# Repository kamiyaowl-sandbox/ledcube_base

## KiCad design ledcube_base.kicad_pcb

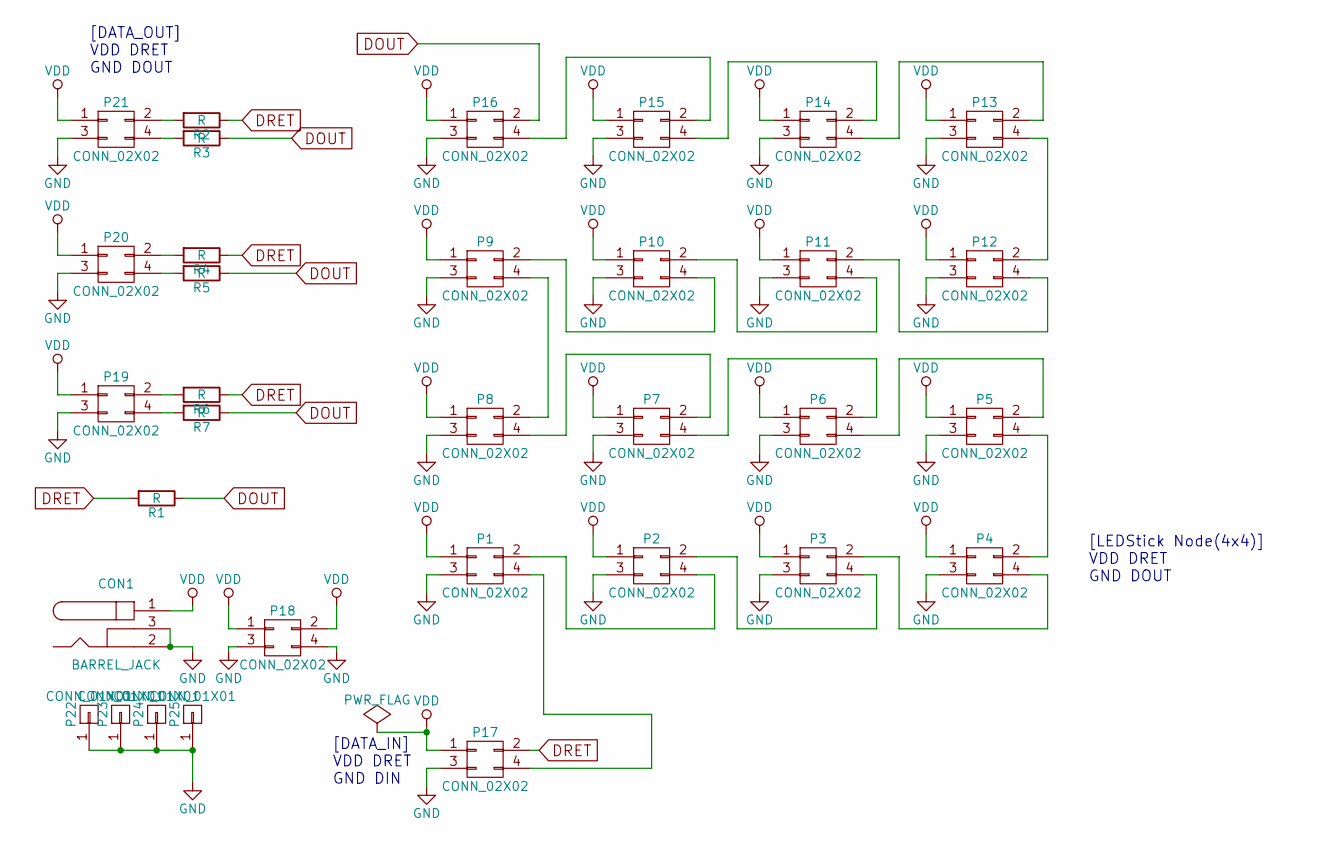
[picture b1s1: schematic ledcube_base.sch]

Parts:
CON1: BARREL_JACK
P1, P2, P3, P4, P5, P6, P7, P8, P9, P10, P11, P12, P13, P14, P15, P16: CONN_02X02; Pin_Header_Straight_2x02
P17: CONN_02X02; Socket_Strip_Angled_2x02
P18: CONN_02X02; Socket_Strip_Straight_2x02
P19, P20, P21: CONN_02X02; Pin_Header_Angled_2x02
P22, P23, P24, P25: CONN_01X01; M3_Drill
R1, R2, R3, R4, R5, R6, R7: R; HANDSOL_0603

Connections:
DOUT: P16.2, R1.1, R3.1, R5.1, R7.1
DRET: P17.2, R1.2, R2.1, R4.1, R6.1
GND: CON1.2, CON1.3, P1.3, P2.3, P3.3, P4.3, P5.3, P6.3, P7.3, P8.3, P9.3, P10.3, P11.3, P12.3, P13.3, P14.3, P15.3, P16.3, P17.3, P18.3, P18.4, P19.3, P20.3, P21.3, P22.1, P23.1, P24.1, P25.1
unnamed: P1.2, P2.4
unnamed: P1.4, P17.4
unnamed: P2.2, P3.4
unnamed: P3.2, P4.4
unnamed: P4.2, P5.4
unnamed: P5.2, P6.4
unnamed: P6.2, P7.4
unnamed: P7.2, P8.4
unnamed: P8.2, P9.4
unnamed: P10.2, P11.4
unnamed: P9.2, P10.4
unnamed: P11.2, P12.4
unnamed: P12.2, P13.4
unnamed: P13.2, P14.4
unnamed: P14.2, P15.4
unnamed: P15.2, P16.4
unnamed: P19.2, R6.2
unnamed: P19.4, R7.2
unnamed: P20.2, R4.2
unnamed: P20.4, R5.2
unnamed: P21.2, R2.2
unnamed: P21.4, R3.2
VDD: CON1.1, P1.1, P2.1, P3.1, P4.1, P5.1, P6.1, P7.1, P8.1, P9.1, P10.1, P11.1, P12.1, P13.1, P14.1, P15.1, P16.1, P17.1, P18.1, P18.2, P19.1, P20.1, P21.1

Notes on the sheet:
[LEDStick Node(4x4)] VDD DRET GND DOUT
[DATA_IN] VDD DRET GND DIN
[DATA_OUT] VDD DRET GND DOUT

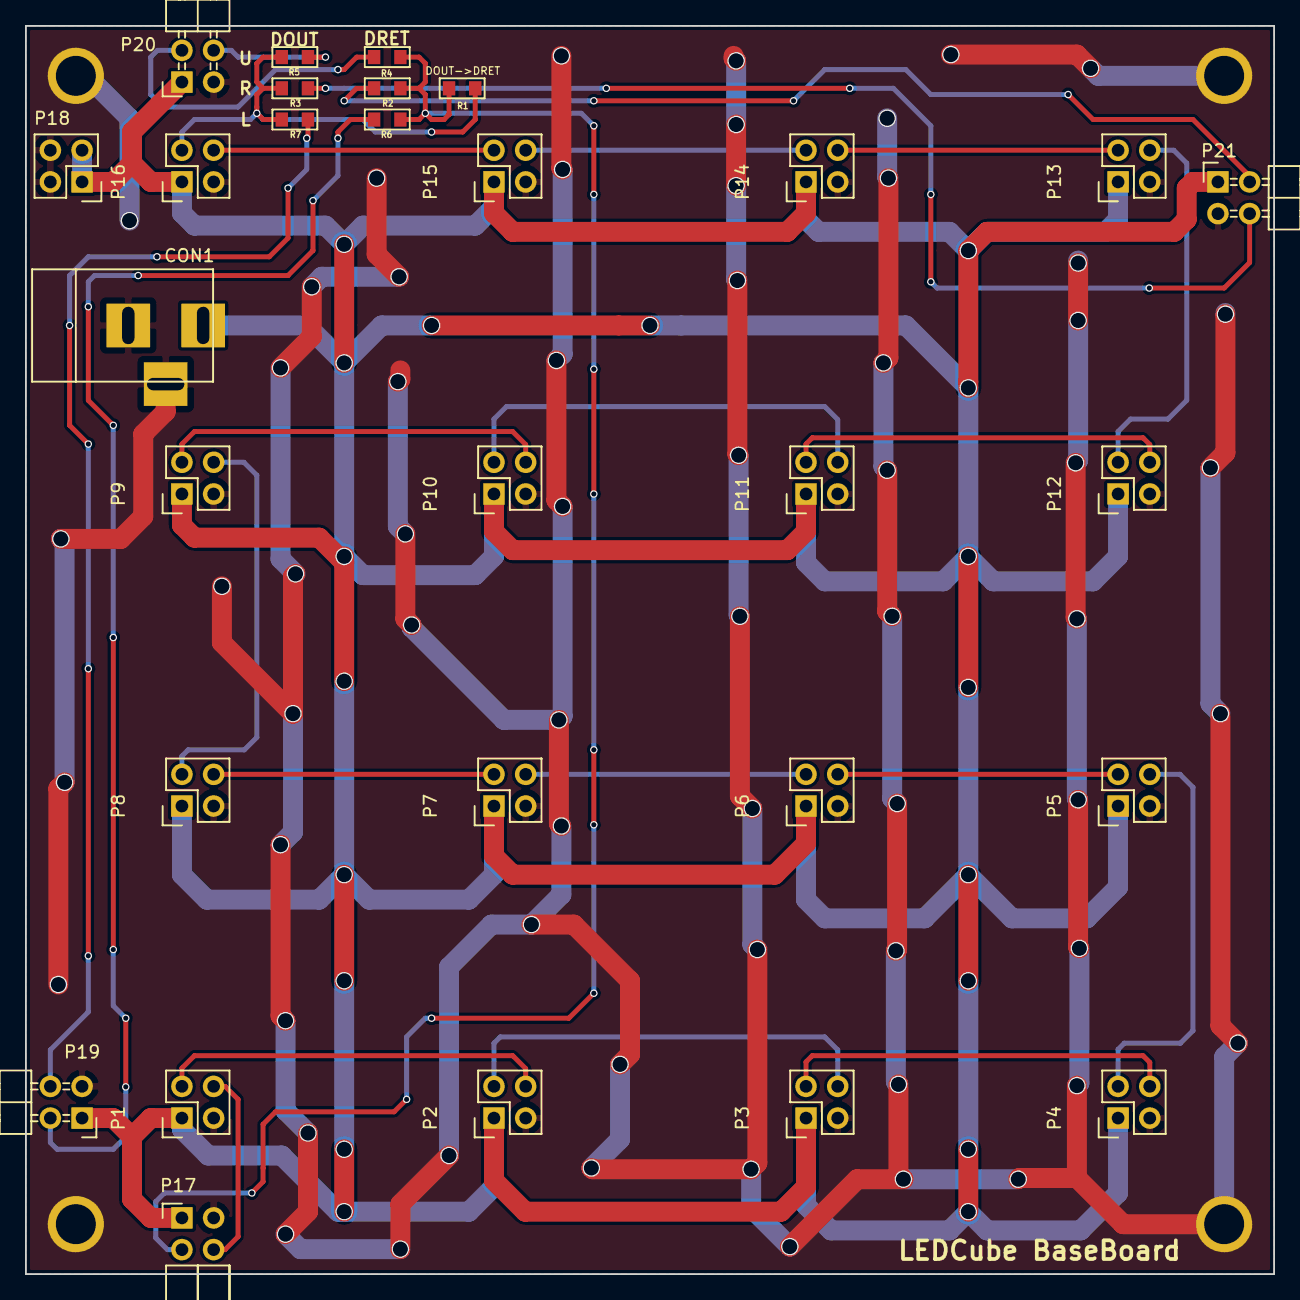
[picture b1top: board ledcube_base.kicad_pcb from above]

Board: 2 copper layers, 100.0 x 100.0 mm, 33 parts (0 on the bottom side), 26 nets.

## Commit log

2016-01-10 Fixed: Via Drill Size
